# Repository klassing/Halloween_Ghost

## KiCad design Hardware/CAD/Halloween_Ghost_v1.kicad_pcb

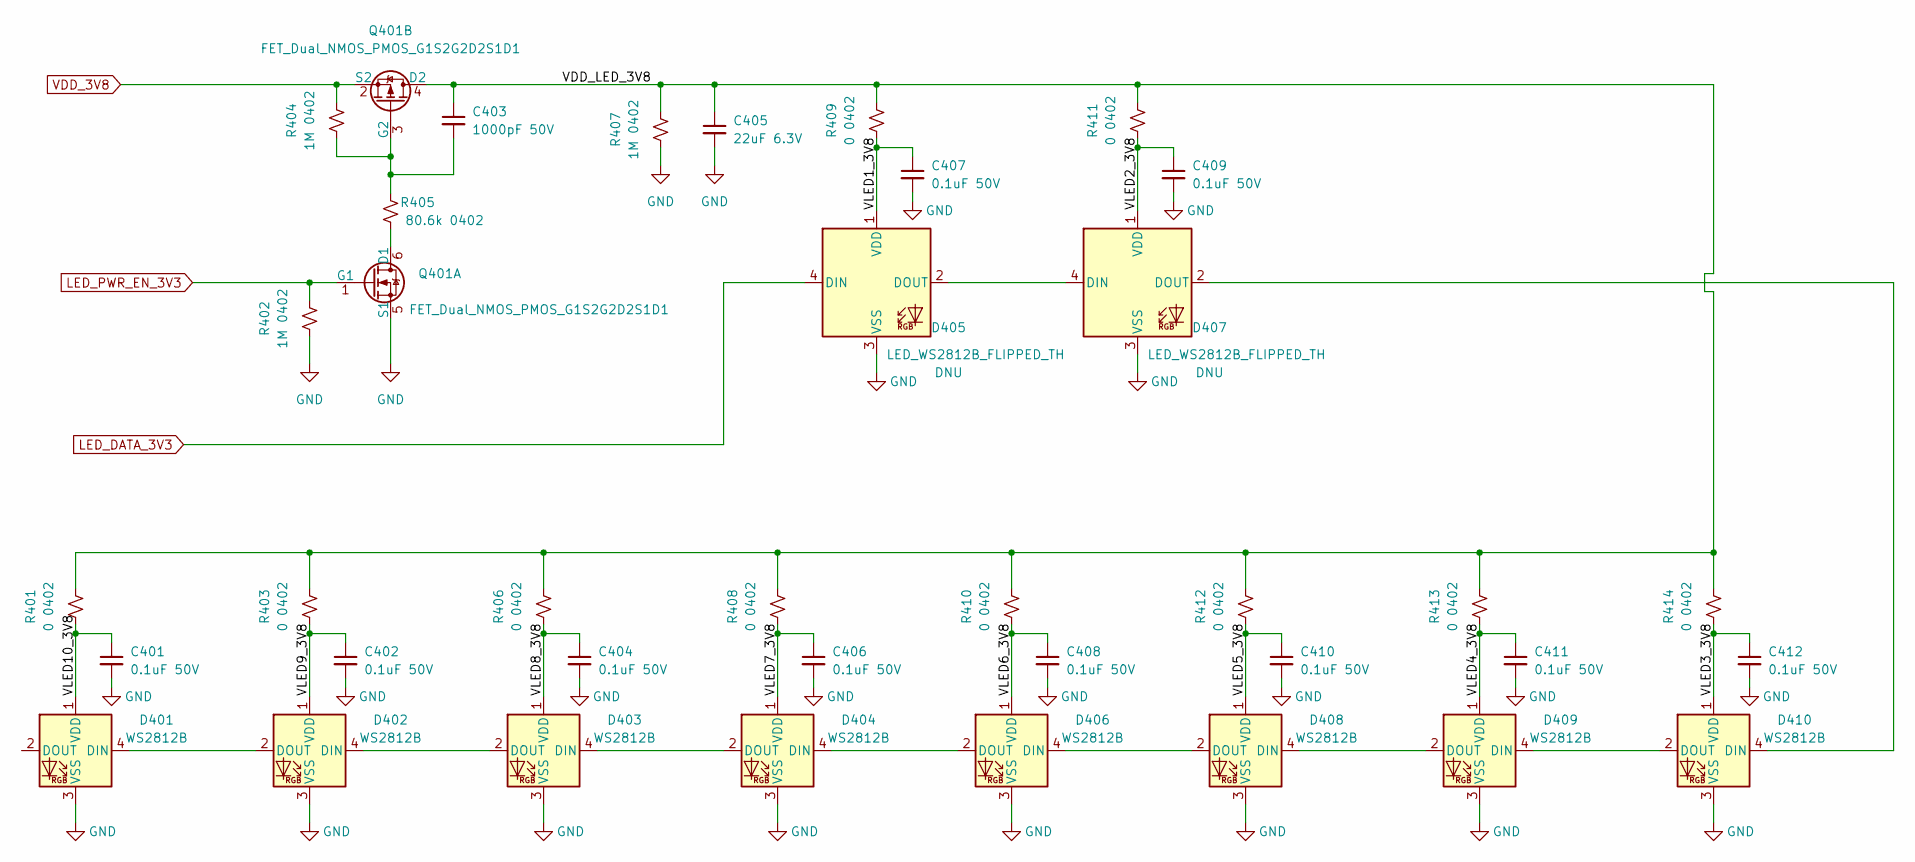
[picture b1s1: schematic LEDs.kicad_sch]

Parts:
C401, C402, C404, C406, C407, C408, C409, C410, C411, C412: 0.1uF 50V; C_0402_1005Metric; JLC_Cost 0.0061
C403: 1000pF 50V; C_0402_1005Metric; JLC_Cost 0.001
C405: 22uF 6.3V; C_0603_1608Metric; JLC_Cost 0.0044
D401, D402, D403, D404, D406, D408, D409, D410: WS2812B; LED_WS2812B_PLCC4_5.0x5.0mm_P3.2mm; JLC_Cost 0.0962
D405, D407: LED_WS2812B_FLIPPED_TH; Manufacturer_Part_Number WS2812B-V5/W
Q401: FET_Dual_NMOS_PMOS_G1S2G2D2S1D1; TSOT-23-6; JLC_Cost 0.1041
R401, R403, R406, R408, R409, R410, R411, R412, R413, R414: 0 0402; R_0402_1005Metric; JLC_Cost 0.0005
R402, R404, R407: 1M 0402; R_0402_1005Metric; JLC_Cost 0.0005
R405: 80.6k 0402; R_0402_1005Metric; JLC_Cost 0.0005

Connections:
/LEDs/VDD_LED_3V8: C403.1, C405.1, Q401.4 (D2), R401.2, R403.2, R406.2, R407.2, R408.2, R409.2, R410.2, R411.2, R412.2, R413.2, R414.2
/LEDs/VLED1_3V8: C407.1, D405.1 (VDD), R409.1
/LEDs/VLED2_3V8: C409.1, D407.1 (VDD), R411.1
/LEDs/VLED3_3V8: C412.1, D410.1 (VDD), R414.1
/LEDs/VLED4_3V8: C411.1, D409.1 (VDD), R413.1
/LEDs/VLED5_3V8: C410.1, D408.1 (VDD), R412.1
/LEDs/VLED6_3V8: C408.1, D406.1 (VDD), R410.1
/LEDs/VLED7_3V8: C406.1, D404.1 (VDD), R408.1
/LEDs/VLED8_3V8: C404.1, D403.1 (VDD), R406.1
/LEDs/VLED9_3V8: C402.1, D402.1 (VDD), R403.1
/LEDs/VLED10_3V8: C401.1, D401.1 (VDD), R401.1
GND: C401.2, C402.2, C404.2, C405.2, C406.2, C407.2, C408.2, C409.2, C410.2, C411.2, C412.2, D401.3 (VSS), D402.3 (VSS), D403.3 (VSS), D404.3 (VSS), D405.3 (VSS), D406.3 (VSS), D407.3 (VSS), D408.3 (VSS), D409.3 (VSS), D410.3 (VSS), Q401.5 (S1), R402.1, R407.1; also elsewhere on the board
LED_DATA_3V3: D405.4 (DIN); also elsewhere on the board
LED_PWR_EN_3V3: Q401.1 (G1), R402.2; also elsewhere on the board
unnamed: C403.2, Q401.3 (G2), R404.1, R405.2
unnamed: D401.4 (DIN), D402.2 (DOUT)
unnamed: D402.4 (DIN), D403.2 (DOUT)
unnamed: D403.4 (DIN), D404.2 (DOUT)
unnamed: D404.4 (DIN), D406.2 (DOUT)
unnamed: D405.2 (DOUT), D407.4 (DIN)
unnamed: D406.4 (DIN), D408.2 (DOUT)
unnamed: D407.2 (DOUT), D410.4 (DIN)
unnamed: D408.4 (DIN), D409.2 (DOUT)
unnamed: D409.4 (DIN), D410.2 (DOUT)
unnamed: Q401.6 (D1), R405.1
VDD_3V8: Q401.2 (S2), R404.2; also elsewhere on the board

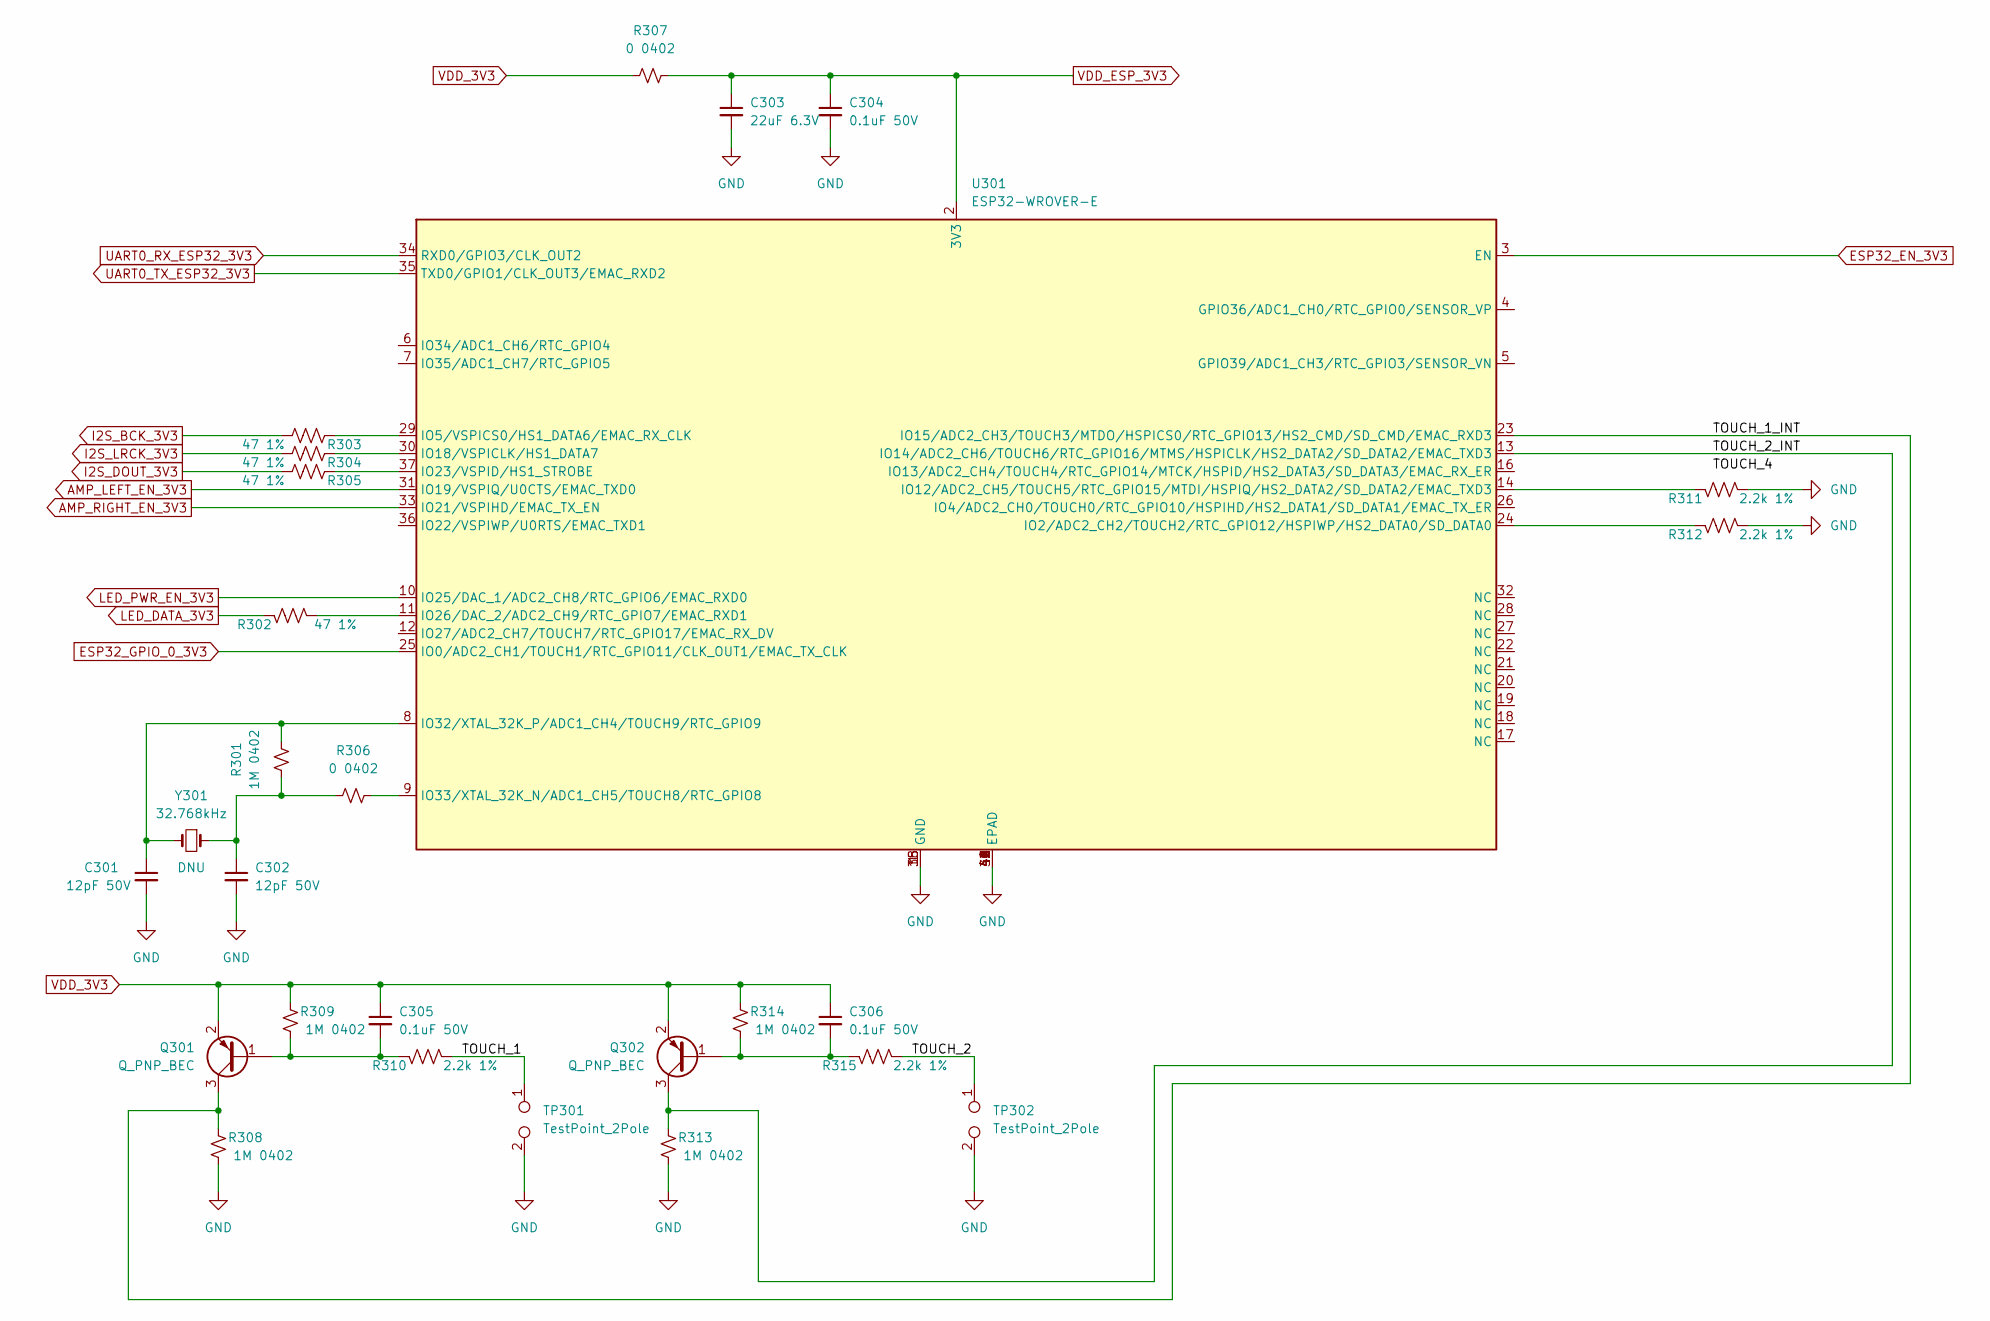
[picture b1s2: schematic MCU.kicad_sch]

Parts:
C301, C302: 12pF 50V; C_0402_1005Metric; JLC_Cost 0.0061
C303: 22uF 6.3V; C_0603_1608Metric; JLC_Cost 0.0044
C304, C305, C306: 0.1uF 50V; C_0402_1005Metric; JLC_Cost 0.0061
Q301, Q302: Q_PNP_BEC; SOT-23; JLC_Cost 0.0147
R301, R308, R309, R313, R314: 1M 0402; R_0402_1005Metric; JLC_Cost 0.0005
R302, R303, R304, R305: 47 1%; R_0402_1005Metric; Manufacturer_Part_Number RMC10K470FTH; Mouser Part Number 791-RMC10K470FTH
R306, R307: 0 0402; R_0402_1005Metric; JLC_Cost 0.0005
R310, R311, R312, R315: 2.2k 1%; R_0402_1005Metric; Manufacturer_Part_Number RMC10K222FTH; Mouser Part Number 791-RMC10K222FTH
TP301, TP302: TestPoint_2Pole
U301: ESP32-WROVER-E; JLC_MPN ESP32-WROVER-E-N8R8
Y301: 32.768kHz; Crystal_SMD_3215-2Pin_3.2x1.5mm; JLC_Cost 0.2034

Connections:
/MCU/TOUCH_1: R310.1, TP301.1
/MCU/TOUCH_1_INT: Q301.3 (C), R308.1, U301.23 (IO15/ADC2_CH3/TOUCH3/MTDO/HSPICS0/RTC_G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)
/MCU/TOUCH_2: R315.1, TP302.1
/MCU/TOUCH_2_INT: Q302.3 (C), R313.1, U301.13 (IO14/ADC2_CH6/TOUCH6/RTC_GPIO16/MTMS/HS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)
AMP_LEFT_EN_3V3: U301.31 (IO19/VSPIQ/U0CTS/EMAC_TXD0); also elsewhere on the board
AMP_RIGHT_EN_3V3: U301.33 (IO21/VSPIHD/EMAC_TX_EN); also elsewhere on the board
ESP32_EN_3V3: U301.3 (EN); also elsewhere on the board
ESP32_GPIO_0_3V3: U301.25 (IO0/ADC2_CH1/TOUCH1/RTC_GPIO11/CLK_OUT1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); also elsewhere on the board
GND: C301.2, C302.2, C303.2, C304.2, R308.2, R311.1, R312.1, R313.2, TP301.2, TP302.2, U301.1 (GND), U301.15 (GND), U301.38 (GND), U301.39 (EPAD), U301.40 (EPAD), U301.41 (EPAD), U301.42 (EPAD), U301.43 (EPAD), U301.44 (EPAD), U301.45 (EPAD), U301.46 (EPAD), U301.47 (EPAD); also elsewhere on the board
I2S_BCK_3V3: R303.1; also elsewhere on the board
I2S_DOUT_3V3: R305.1; also elsewhere on the board
I2S_LRCK_3V3: R304.1; also elsewhere on the board
LED_DATA_3V3: R302.2; also elsewhere on the board
LED_PWR_EN_3V3: U301.10 (IO25/DAC_1/ADC2_CH8/RTC_GPIO6/EMAC_RXD0); also elsewhere on the board
unnamed: C301.1, R301.2, U301.8 (IO32/XTAL_32K_P/ADC1_CH4/TOUCH9/RTC_GPI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), Y301.2
unnamed: C302.1, R301.1, R306.1, Y301.1
unnamed: C305.2, Q301.1 (B), R309.2, R310.2
unnamed: C306.2, Q302.1 (B), R314.2, R315.2
unnamed: R302.1, U301.11 (IO26/DAC_2/ADC2_CH9/RTC_GPIO7/EMAC_RXD1)
unnamed: R303.2, U301.29 (IO5/VSPICS0/HS1_DATA6/EMAC_RX_CLK)
unnamed: R304.2, U301.30 (IO18/VSPICLK/HS1_DATA7)
unnamed: R305.2, U301.37 (IO23/VSPID/HS1_STROBE)
unnamed: R306.2, U301.9 (IO33/XTAL_32K_N/ADC1_CH5/TOUCH8/RTC_GPI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)
unnamed: R311.2, U301.14 (IO12/ADC2_CH5/TOUCH5/RTC_GPIO15/MTDI/HS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)
unnamed: R312.2, U301.24 (IO2/ADC2_CH2/TOUCH2/RTC_GPIO12/HSPIWP/H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)
UART0_RX_ESP32_3V3: U301.34 (RXD0/GPIO3/CLK_OUT2); also elsewhere on the board
UART0_TX_ESP32_3V3: U301.35 (TXD0/GPIO1/CLK_OUT3/EMAC_RXD2); also elsewhere on the board
VDD_3V3: C305.1, C306.1, Q301.2 (E), Q302.2 (E), R307.1, R309.1, R314.1; also elsewhere on the board
VDD_ESP_3V3: C303.1, C304.1, R307.2, U301.2 (3V3)

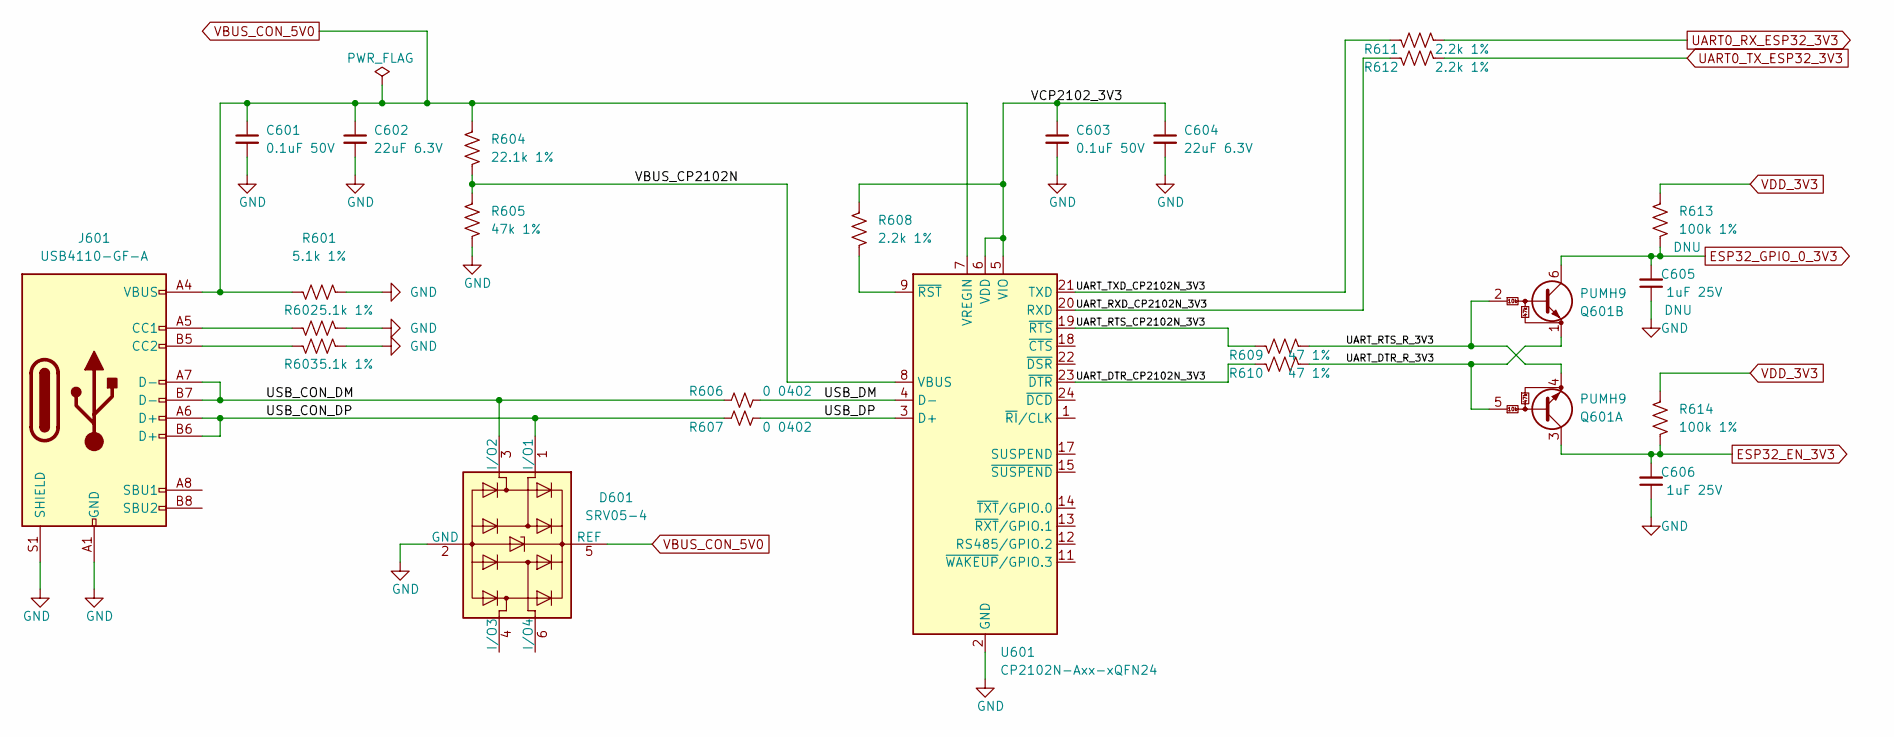
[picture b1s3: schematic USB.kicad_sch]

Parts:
C601, C603: 0.1uF 50V; C_0402_1005Metric; JLC_Cost 0.0061
C602, C604: 22uF 6.3V; C_0603_1608Metric; JLC_Cost 0.0044
C605, C606: 1uF 25V; C_0402_1005Metric; JLC_Type Basic
D601: SRV05-4; SOT-23-6; JLC_Cost 0.1181
J601: USB4110-GF-A; JLC_Cost 0.1104
Q601: PUMH9; SOT-363_SC-70-6; Manufacturer_Part_Number PUMH9,115; Mouser Part Number 771-PUMH9-T/R
R601, R602, R603: 5.1k 1%; R_0402_1005Metric; Manufacturer_Part_Number RMC10K512FTH; Mouser Part Number 791-RMC10K512FTH
R604: 22.1k 1%; R_0402_1005Metric; Manufacturer_Part_Number RC0402FR-0722K1L; Mouser Part Number 603-RC0402FR-0722K1L
R605: 47k 1%; R_0402_1005Metric; Manufacturer_Part_Number RMC10K473FTH; Mouser Part Number 791-RMC10K473FTH
R606, R607: 0 0402; R_0402_1005Metric; JLC_Cost 0.0005
R608, R611, R612: 2.2k 1%; R_0402_1005Metric; Manufacturer_Part_Number RMC10K222FTH; Mouser Part Number 791-RMC10K222FTH
R609, R610: 47 1%; R_0402_1005Metric; Manufacturer_Part_Number RMC10K470FTH; Mouser Part Number 791-RMC10K470FTH
R613, R614: 100k 1%; R_0402_1005Metric; Manufacturer_Part_Number RMC10K104FTH; Mouser Part Number 791-RMC10K104FTH
U601: CP2102N-Axx-xQFN24; QFN-24-1EP_4x4mm_P0.5mm_EP2.6x2.6mm; Manufacturer_Part_Number CP2102N-A02-GQFN24; Mouser Part Number 634-CP2102NA02GQFN24

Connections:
/USB/UART_DTR_CP2102N_3V3: R610.2, U601.23 (~DTR)
/USB/UART_DTR_R_3V3: Q601.1 (E2), Q601.5 (B1), R610.1
/USB/UART_RTS_CP2102N_3V3: R609.2, U601.19 (~RTS)
/USB/UART_RTS_R_3V3: Q601.2 (B2), Q601.4 (E1), R609.1
/USB/UART_RXD_CP2102N_3V3: R612.2, U601.20 (RXD)
/USB/UART_TXD_CP2102N_3V3: R611.2, U601.21 (TXD)
/USB/USB_CON_DM: D601.3 (I/O2), J601.A7 (D-), J601.B7 (D-), R606.1
/USB/USB_CON_DP: D601.1 (I/O1), J601.A6 (D+), J601.B6 (D+), R607.1
/USB/USB_DM: R606.2, U601.4 (D-)
/USB/USB_DP: R607.2, U601.3 (D+)
/USB/VBUS_CP2102N: R604.2, R605.1, U601.8 (VBUS)
/USB/VCP2102_3V3: C603.1, C604.1, R608.1, U601.5 (VIO), U601.6 (VDD)
ESP32_EN_3V3: C606.2, Q601.3 (C1), R614.2; also elsewhere on the board
ESP32_GPIO_0_3V3: C605.2, Q601.6 (C2), R613.2; also elsewhere on the board
GND: C601.2, C602.2, C603.2, C604.2, C605.1, C606.1, D601.2 (GND), J601.A1 (GND), J601.A12 (GND), J601.B1 (GND), J601.B12 (GND), J601.S1 (SHIELD), R601.2, R602.1, R603.1, R605.2, U601.2 (GND), U601.25 (GND); also elsewhere on the board
unnamed: J601.A5 (CC1), R602.2
unnamed: J601.B5 (CC2), R603.2
unnamed: R608.2, U601.9 (~RST)
UART0_RX_ESP32_3V3: R611.1; also elsewhere on the board
UART0_TX_ESP32_3V3: R612.1; also elsewhere on the board
VBUS_CON_5V0: C601.1, C602.1, D601.5 (REF), J601.A4 (VBUS), J601.A9 (VBUS), J601.B4 (VBUS), J601.B9 (VBUS), R601.1, R604.1, U601.7 (VREGIN); also elsewhere on the board
VDD_3V3: R613.1, R614.1; also elsewhere on the board

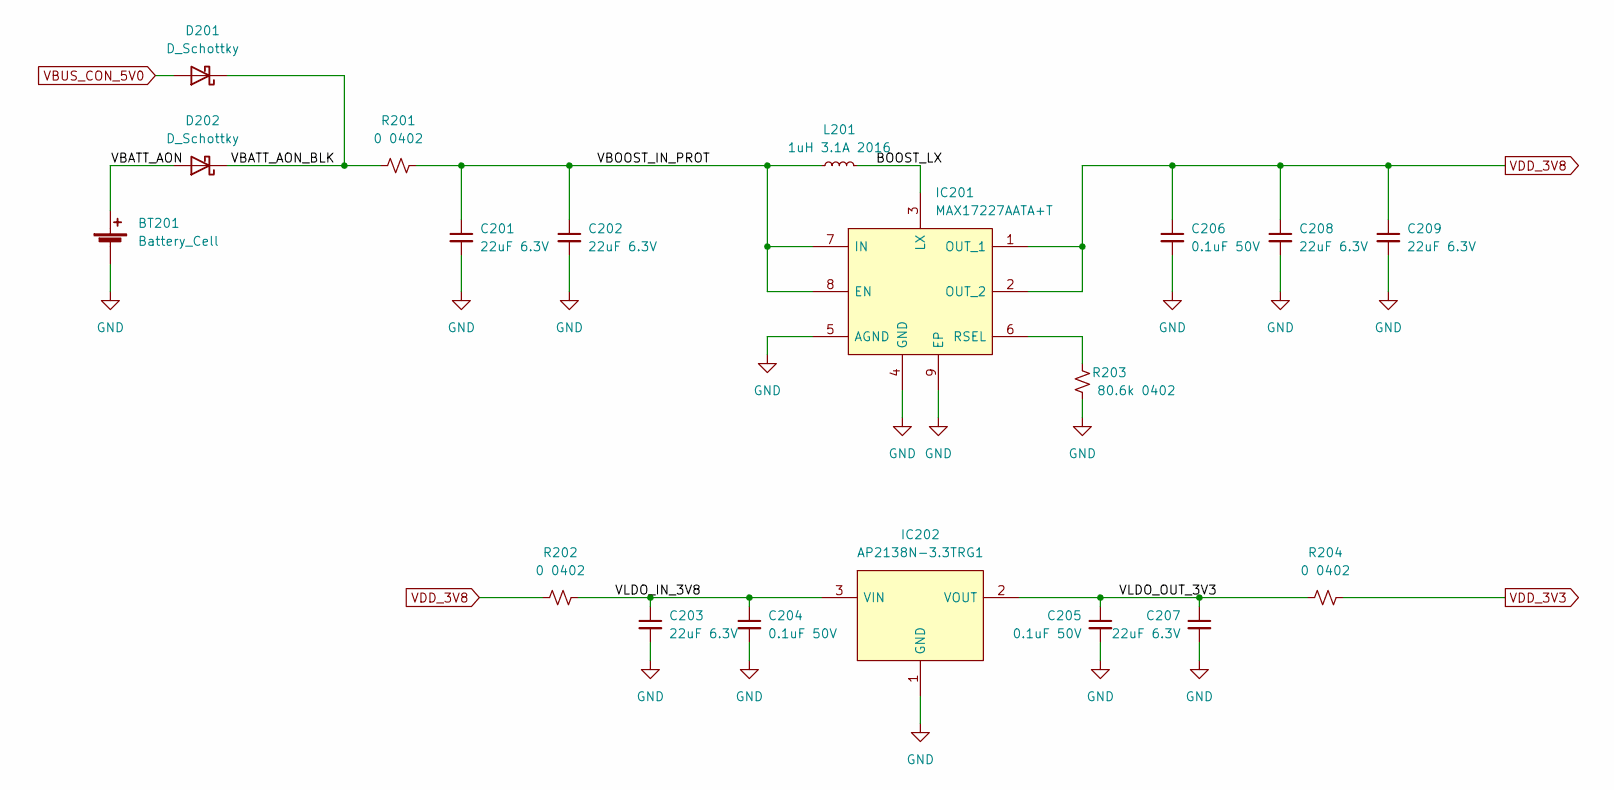
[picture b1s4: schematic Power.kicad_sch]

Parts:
BT201: Battery_Cell; BatteryHolder_Keystone_1128_1xCR123A_lifted; Manufacturer_Part_Number 1128
C201, C202, C203, C207, C208, C209: 22uF 6.3V; C_0603_1608Metric; JLC_Cost 0.0044
C204, C205, C206: 0.1uF 50V; C_0402_1005Metric; JLC_Cost 0.0061
D201, D202: D_Schottky; D_SOD-323; JLC_Cost 0.0147
IC201: MAX17227AATA+T; TDFN-8-EP_2.0x2.0x0.80_P0.5mm; Mouser Part Number 700-MAX17227AATA+T
IC202: AP2138N-3.3TRG1; SOT-23-3_DiodesINC; Mouser Part Number 621-AP2138N-3.3TRG1
L201: 1uH 3.1A 2016; L_0806_2016Metric; JLC_Cost 0.0975
R201, R202, R204: 0 0402; R_0402_1005Metric; JLC_Cost 0.0005
R203: 80.6k 0402; R_0402_1005Metric; JLC_Cost 0.0005

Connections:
/Power/BOOST_LX: IC201.3 (LX), L201.2
/Power/VBATT_AON: BT201.1 (+), D202.2 (A)
/Power/VBATT_AON_BLK: D201.1 (K), D202.1 (K), R201.1
/Power/VBOOST_IN_PROT: C201.1, C202.1, IC201.7 (IN), IC201.8 (EN), L201.1, R201.2
/Power/VLDO_IN_3V8: C203.1, C204.1, IC202.3 (VIN), R202.2
/Power/VLDO_OUT_3V3: C205.1, C207.1, IC202.2 (VOUT), R204.1
GND: BT201.2 (-), C201.2, C202.2, C203.2, C204.2, C205.2, C206.2, C207.2, C208.2, C209.2, IC201.4 (GND), IC201.5 (AGND), IC201.9 (EP), IC202.1 (GND), R203.1; also elsewhere on the board
unnamed: IC201.6 (RSEL), R203.2
VBUS_CON_5V0: D201.2 (A); also elsewhere on the board
VDD_3V3: R204.2; also elsewhere on the board
VDD_3V8: C206.1, C208.1, C209.1, IC201.1 (OUT_1), IC201.2 (OUT_2), R202.1; also elsewhere on the board

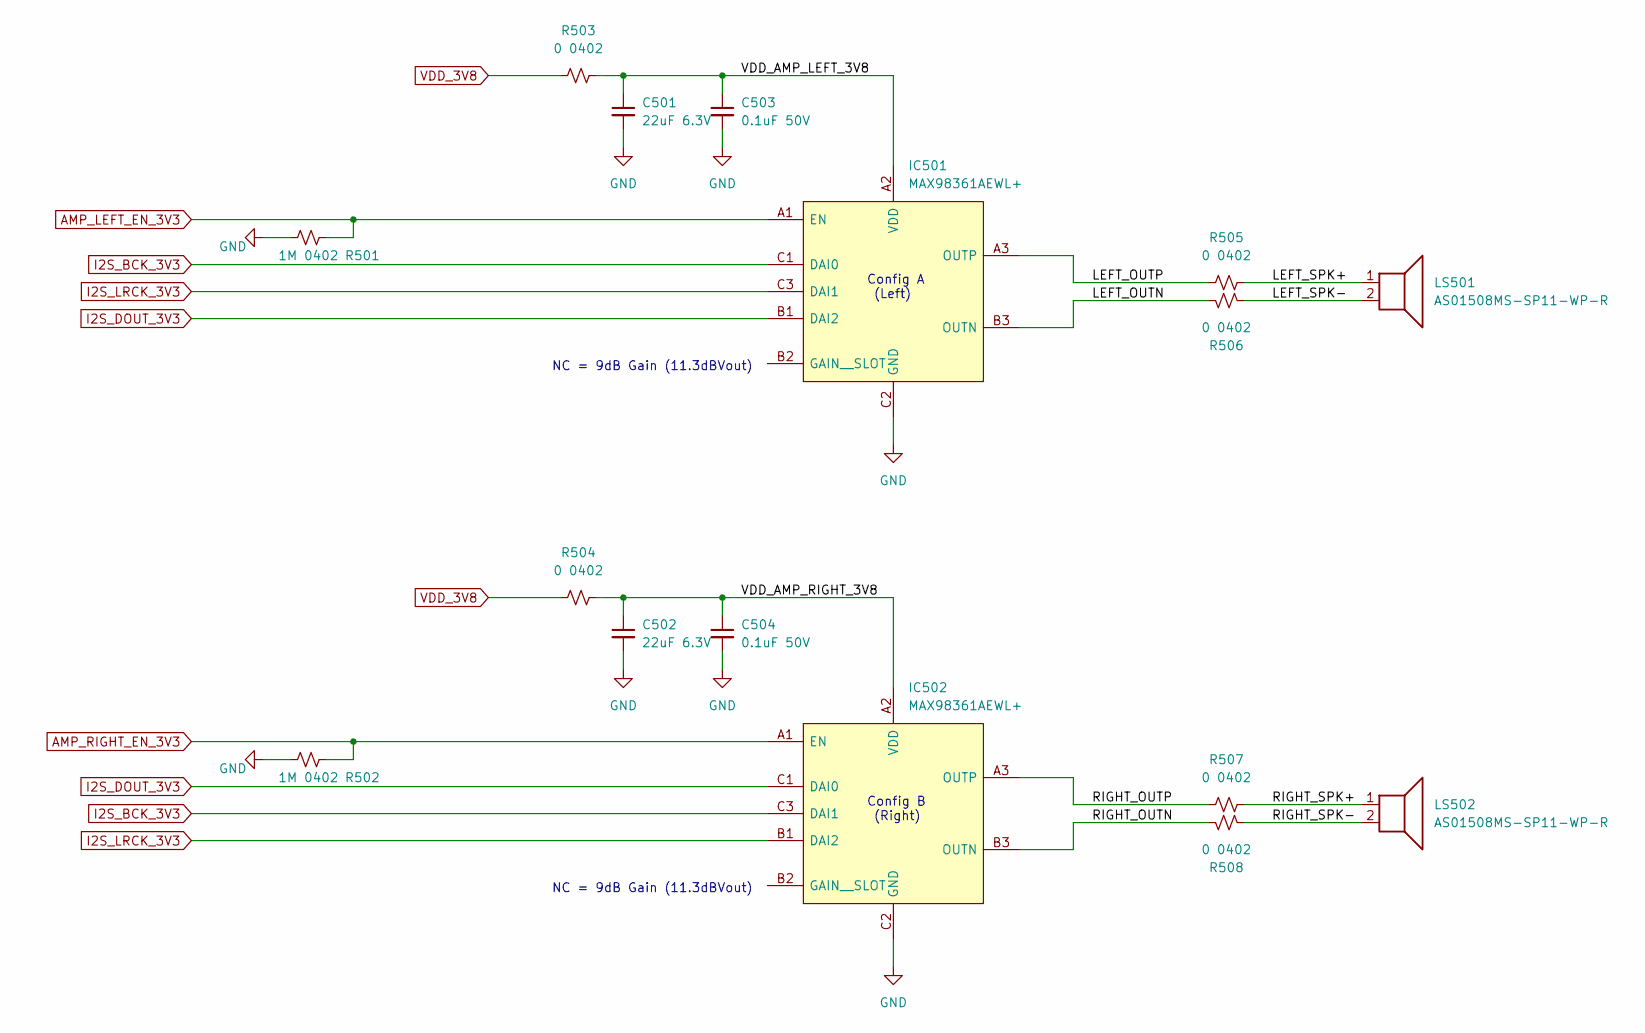
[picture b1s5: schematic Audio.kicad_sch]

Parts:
C501, C502: 22uF 6.3V; C_0603_1608Metric; JLC_Cost 0.0044
C503, C504: 0.1uF 50V; C_0402_1005Metric; JLC_Cost 0.0061
IC501, IC502: MAX98361AEWL+; BGA9C40P3X3_144X135X69; Manufacturer_Part_Number MAX98361AEWL+
LS501, LS502: AS01508MS-SP11-WP-R
R501, R502: 1M 0402; R_0402_1005Metric; JLC_Cost 0.0005
R503, R504, R505, R506, R507, R508: 0 0402; R_0402_1005Metric; JLC_Cost 0.0005

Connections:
/Audio/LEFT_OUTN: IC501.B3 (OUTN), R506.1
/Audio/LEFT_OUTP: IC501.A3 (OUTP), R505.1
/Audio/LEFT_SPK+: LS501.1, R505.2
/Audio/LEFT_SPK-: LS501.2, R506.2
/Audio/RIGHT_OUTN: IC502.B3 (OUTN), R508.1
/Audio/RIGHT_OUTP: IC502.A3 (OUTP), R507.1
/Audio/RIGHT_SPK+: LS502.1, R507.2
/Audio/RIGHT_SPK-: LS502.2, R508.2
/Audio/VDD_AMP_LEFT_3V8: C501.1, C503.1, IC501.A2 (VDD), R503.2
/Audio/VDD_AMP_RIGHT_3V8: C502.1, C504.1, IC502.A2 (VDD), R504.2
AMP_LEFT_EN_3V3: IC501.A1 (EN), R501.1; also elsewhere on the board
AMP_RIGHT_EN_3V3: IC502.A1 (EN), R502.1; also elsewhere on the board
GND: C501.2, C502.2, C503.2, C504.2, IC501.C2 (GND), IC502.C2 (GND), R501.2, R502.2; also elsewhere on the board
I2S_BCK_3V3: IC501.C1 (DAI0), IC502.C3 (DAI1); also elsewhere on the board
I2S_DOUT_3V3: IC501.B1 (DAI2), IC502.C1 (DAI0); also elsewhere on the board
I2S_LRCK_3V3: IC501.C3 (DAI1), IC502.B1 (DAI2); also elsewhere on the board
VDD_3V8: R503.1, R504.1; also elsewhere on the board

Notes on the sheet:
NC = 9dB Gain (11.3dBVout)
Config A (Left)
Config B (Right)

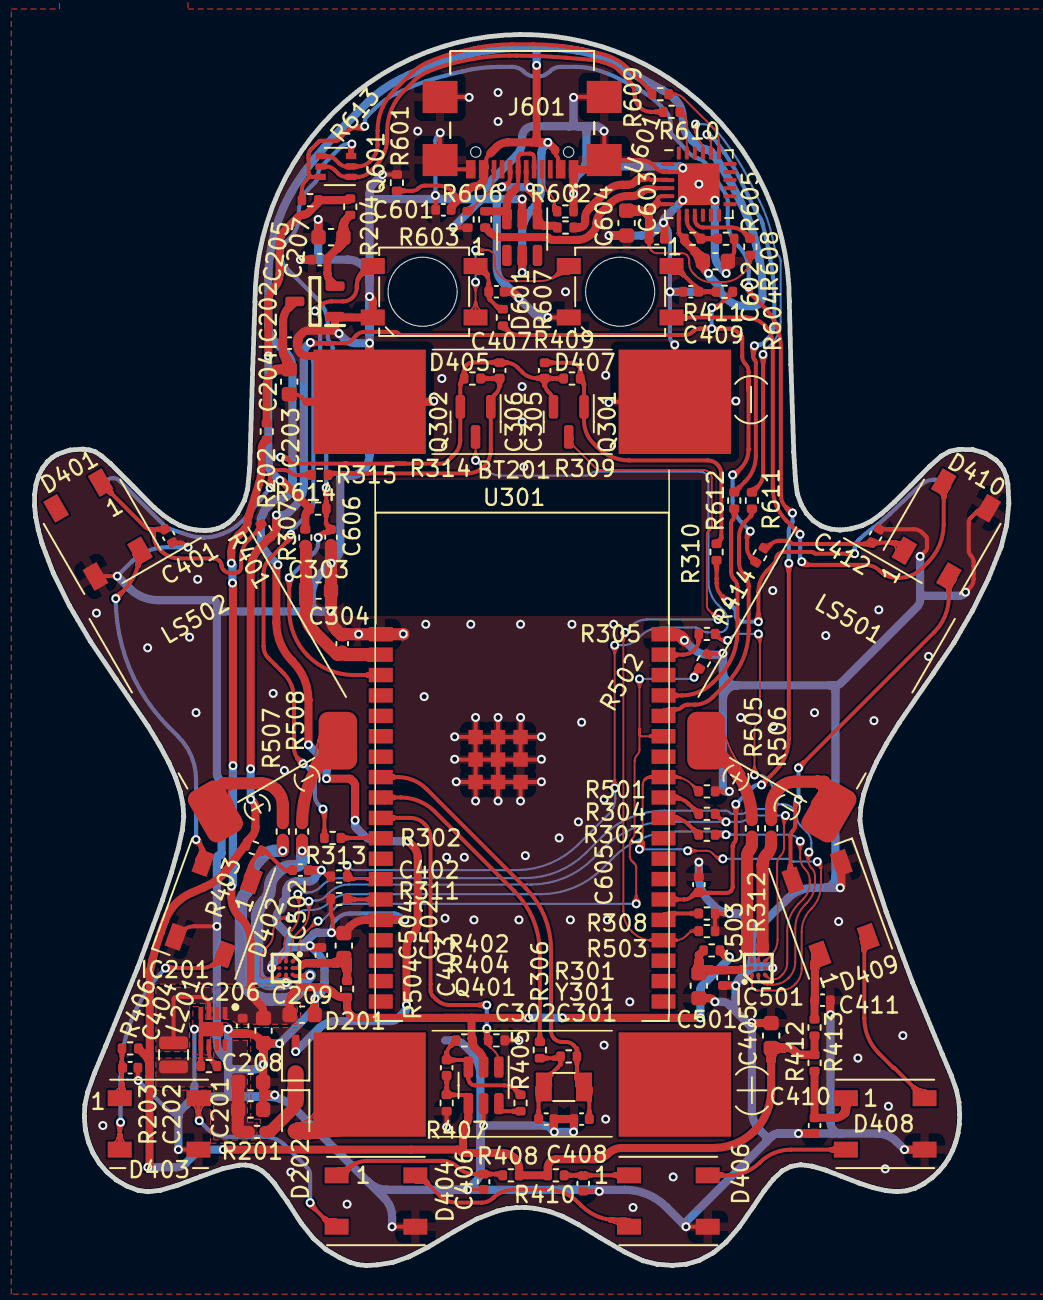
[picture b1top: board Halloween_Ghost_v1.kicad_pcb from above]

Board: 2 copper layers, 60.7 x 76.6 mm, 121 parts (0 on the bottom side), 83 nets.

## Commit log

2022-10-20 Initial_Release
2022-10-21 v0.0.1 release
2022-10-24 power reduction
2022-11-13 updated SW to PlatformIO
